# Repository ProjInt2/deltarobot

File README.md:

# Delta Robot Actuation Project

*by Lucas Camargo, Soly Waltrick, and Willian Kenji Nishizawa*

This project consists in the development of a driving and control solution for a standard delta robot. It does not concern the development of the robot itself, or its actuators. It focuses on driving the actuators, control mechanisms, and required transducers (sensors).

The deliverables are organized in the following directories:

+ *datasheets* - documentation on different components used in the project
+ *fw* - controller + driver: board firmware
+ *hw* - controller + driver: hardware project
+ *report* - project report
+ *sw* - interface software for interacting with the controller board using a computer

*TODO: insert backref link to post*

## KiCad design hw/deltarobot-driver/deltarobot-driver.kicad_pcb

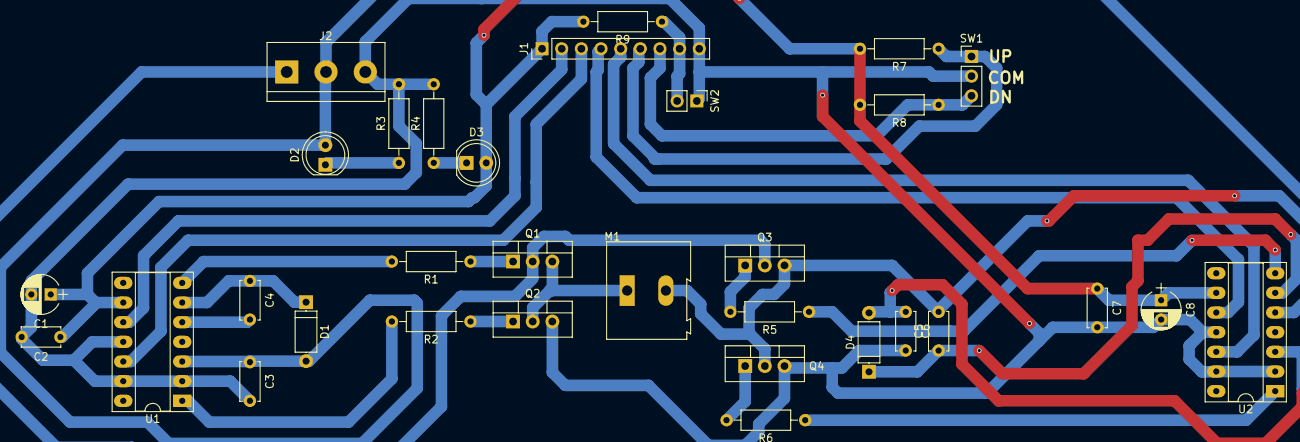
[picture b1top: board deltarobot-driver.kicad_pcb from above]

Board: 2 copper layers, 32 parts (0 on the bottom side), 25 nets.

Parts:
C1, C8: .47uF; CP_Radial_D5.0mm_P2.50mm
C2, C7: .1uF; C_Disc_D5.0mm_W2.5mm_P5.00mm
C3, C6: 2.2u; C_Disc_D5.0mm_W2.5mm_P5.00mm
C4, C5: 100u; C_Disc_D5.0mm_W2.5mm_P5.00mm
D1, D4: D; D_A-405_P7.62mm_Horizontal
D2: LED_vcc; LED_D5.0mm
D3: LED_vdd; LED_D5.0mm
J1: CONN_SIG; Pin_Header_Straight_1x09_Pitch2.54mm
J2: CONN_PWR; TerminalBlock_bornier-3_P5.08mm
M1: Motor_DC; TerminalBlock_Altech_AK300-2_P5.00mm
Q1, Q2, Q3, Q4: IRFZ44N; TO-220-3_Vertical
R1, R2, R5, R6: 0R; R_Axial_DIN0207_L6.3mm_D2.5mm_P10.16mm_Horizontal
R3, R4: R; R_Axial_DIN0207_L6.3mm_D2.5mm_P10.16mm_Horizontal
R7, R8, R9: 10k; R_Axial_DIN0207_L6.3mm_D2.5mm_P10.16mm_Horizontal
SW1: Rotary_Encoder; Pin_Header_Straight_1x03_Pitch2.54mm
SW2: SW_STOP; Pin_Header_Straight_1x02_Pitch2.54mm
U1, U2: IR2010; DIP-14_W7.62mm_Socket_LongPads

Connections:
+12V: J2.1, Q1.2, Q3.2
/Ha: J1.2, U1.10
/Hb: J1.4, U2.10
/La: J1.3, U1.12
/Lb: J1.5, U2.12
/Sdn: J1.7, R8.1, SW1.3
/Sstop: J1.8, R9.1, SW2.2
/Sup: J1.6, R7.1, SW1.1
GND: C1.2, C2.2, C3.2, C6.2, C7.2, C8.2, J1.9, J2.3, Q2.3, Q4.3, R3.2, R4.2, SW1.2, SW2.1, U1.2, U1.11, U1.13, U2.2, U2.11, U2.13
unnamed: C4.1, D1.1, U1.6
unnamed: C4.2, M1.1, Q1.3, Q2.2, U1.5
unnamed: C5.1, D4.1, U2.6
unnamed: C5.2, M1.2, Q3.3, Q4.2, U2.5
unnamed: D2.1, R3.1
unnamed: D3.1, R4.1
unnamed: Q1.1, R1.1
unnamed: Q2.1, R2.1
unnamed: Q3.1, R5.2
unnamed: Q4.1, R6.2
unnamed: R1.2, U1.7
unnamed: R2.2, U1.1
unnamed: R5.1, U2.7
unnamed: R6.1, U2.1
VCC: C3.1, C6.1, D1.2, D2.2, D4.2, J2.2, U1.3, U2.3
VDD: C1.1, C2.1, C7.1, C8.1, D3.2, J1.1, R7.2, R8.2, R9.2, U1.9, U2.9

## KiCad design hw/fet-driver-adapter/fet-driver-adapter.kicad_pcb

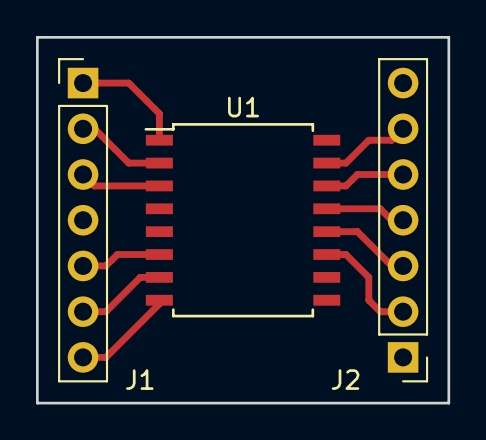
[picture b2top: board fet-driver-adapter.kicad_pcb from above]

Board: 2 copper layers, 22.9 x 20.3 mm, 3 parts (0 on the bottom side), 11 nets.

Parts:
J1: DIP_1_7; Pin_Header_Straight_1x07_Pitch2.54mm
J2: DIP_8_14; Pin_Header_Straight_1x07_Pitch2.54mm
U1: IR210x; SOIC-16W_7.5x10.3mm_Pitch1.27mm

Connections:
/COM: J1.2, U1.2
/HIN: J2.3, U1.12
/HO: J1.7, U1.8
/LIN: J2.5, U1.14
/LO: J1.1, U1.1
/SD: J2.4, U1.13
/VB: J1.6, U1.7
/VS: J1.5, U1.6
/Vcc: J1.3, U1.3
/Vdd: J2.2, U1.11
/Vss: J2.6, U1.15

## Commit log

2018-03-22 added readme
2018-03-22 first file dump, structure definition
2018-03-22 folders for firmware and interface software
2018-03-22 tiva datasheed added
2018-03-22 added authors to readme
2018-03-28 added pictures
2018-03-28 [hw] defined uC pinout and connectivity
2018-04-04 Added controller firmware
2018-06-29 Huge code dump
2018-06-29 added libdeltarobot
2018-06-29 changed ignore files, added doc folder
2018-06-29 added fw to version control
2018-06-29 added more datasheets
2018-06-29 addedlibdeltarobot back symlink
2018-06-29 added report folder flaceholder
2018-06-29 added thru-hole adapter for smd mosfet driver
2018-06-29 added motor driver pcb
2018-06-29 added missing hardware files
2018-07-05 [libdeltarobot] fixed bugs, added test
2018-07-05 [doc] updated protocol spec
2018-07-05 [deltarobot-gui] created basic interface, 3d representation
2018-08-07 progress in all fronts, specially software
2018-08-07 Added missing files
2018-12-04 3d print parts for motor replacement, first working version of sotfware and firmware
